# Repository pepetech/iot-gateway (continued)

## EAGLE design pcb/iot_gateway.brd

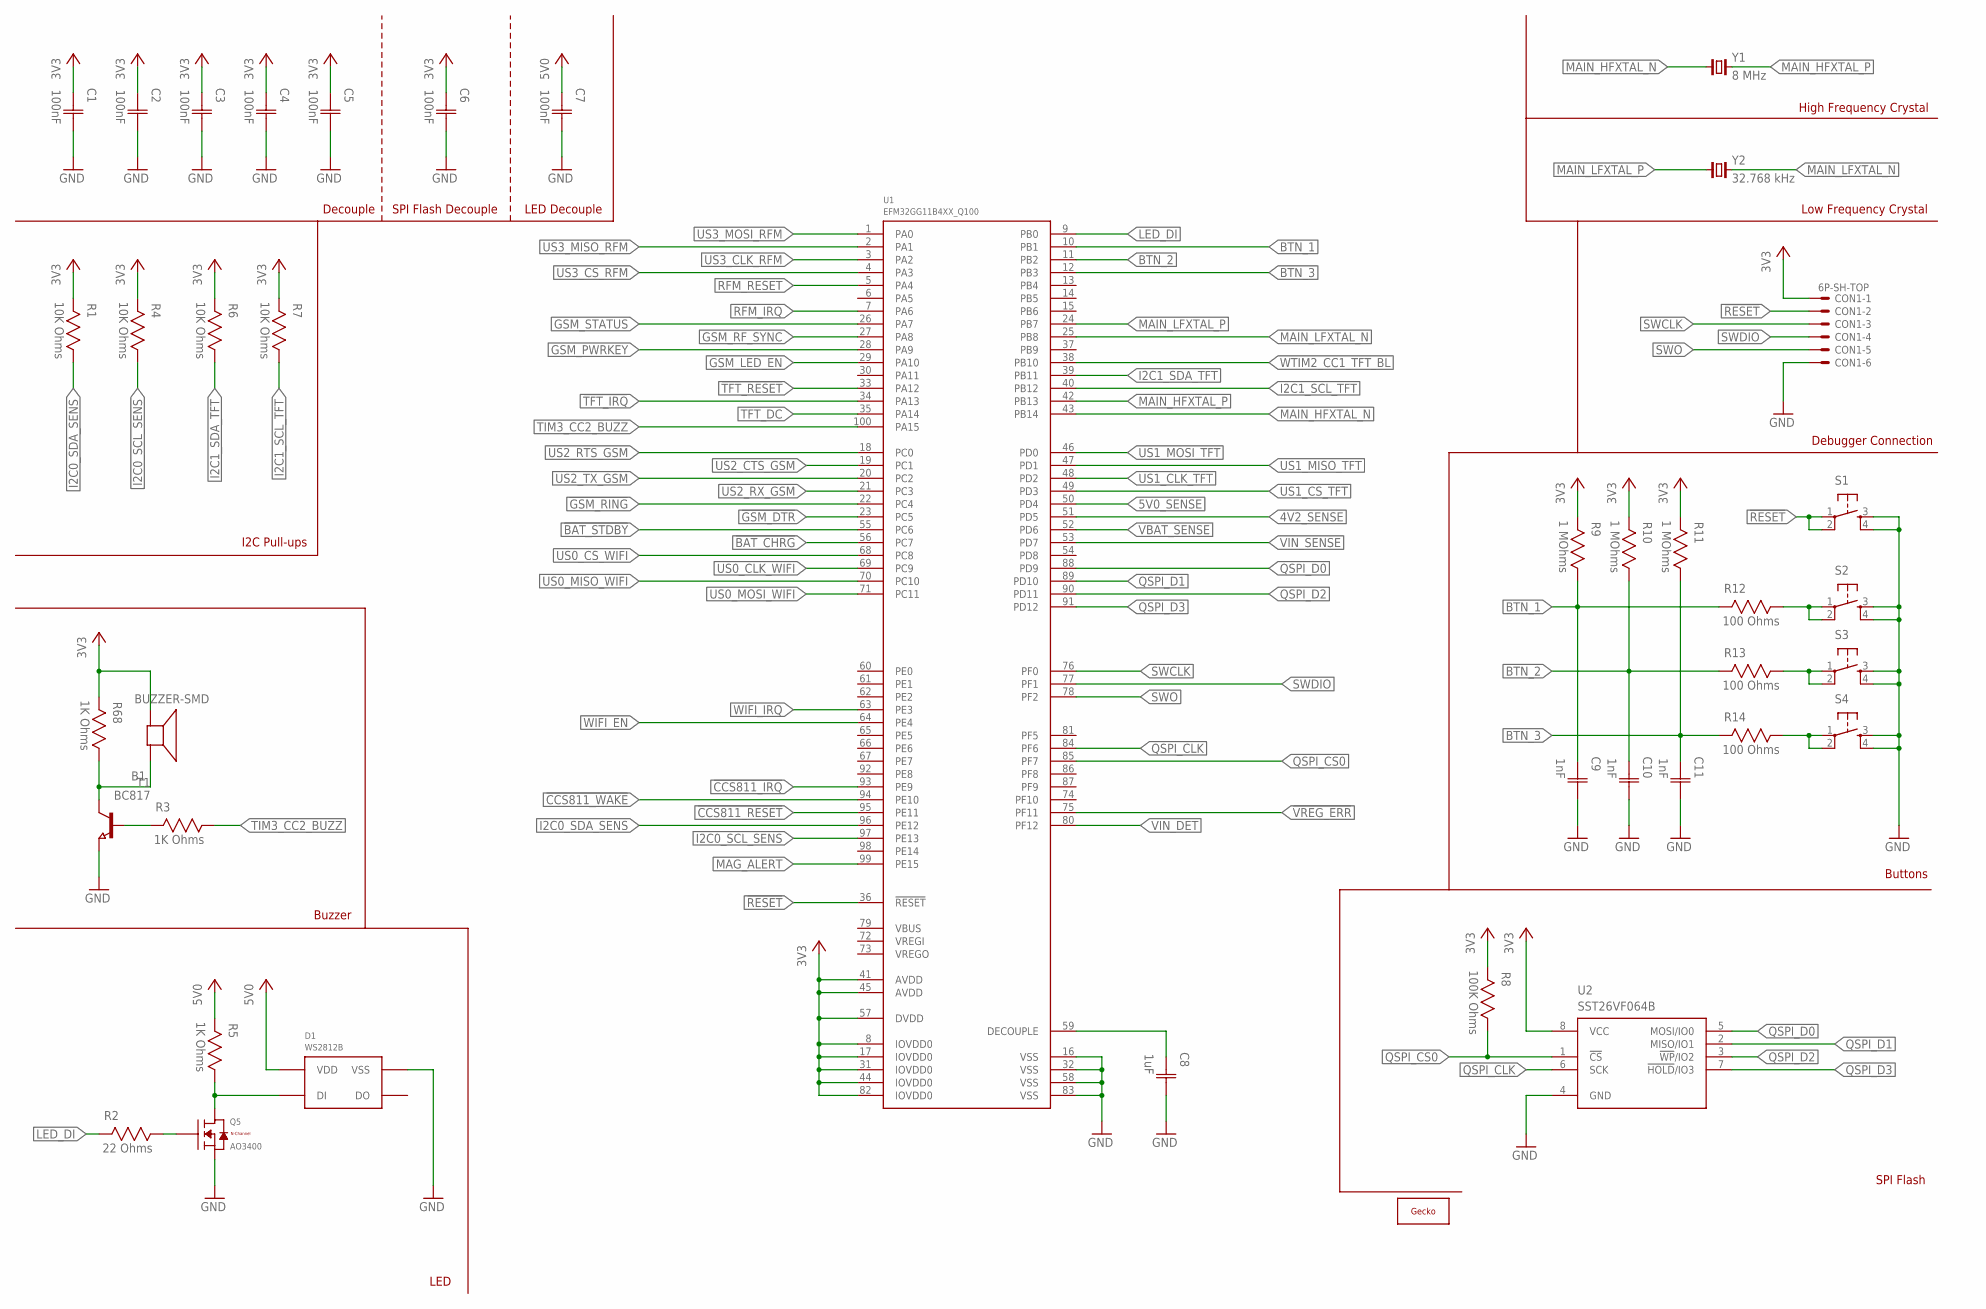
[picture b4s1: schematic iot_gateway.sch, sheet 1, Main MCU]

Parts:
B1: BUZZER-SMD; SMD
C1, C2, C3, C4, C5, C6, C7: 100nF; CAP0603
C8: 1uF; CAP0603
C9, C10, C11: 1nF; CAP0603
CON1: 6P-SH-TOP; SH-06-TOP
D1: WS2812B; WS2812B-SMD5050
Q5: AO3400; SOT23
R1, R4, R6, R7: 10K Ohms; RES0603
R2: 22 Ohms; RES0603
R3, R5, R68: 1K Ohms; RES0603
R8: 100K Ohms; RES0603
R9, R10, R11: 1 MOhms; RES0603
R12, R13, R14: 100 Ohms; RES0603
S1: TAC_SWITCHSMD; TAC_SW_SMD_RESET
S2, S3, S4: TAC_SWITCHSMD_4.5X4.5; TAC_SW_SMD_4.5X4.5
T1: BC817; SOT23
U1: EFM32GG11B4XX_Q100; QFP100
U2: SST26VF064B; WSOIC8
U$1: GECKO
Y1: 8 MHz; 2-SMD-5X3
Y2: 32.768 kHz; CM200S

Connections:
3V3: B1.1 (+), C1.1 (C1), C2.1 (C1), C3.1 (C1), C4.1 (C1), C5.1 (C1), C6.1 (C1), CON1.1, R1.2, R4.2, R6.2, R7.2, R8.2, R9.2, R10.2, R11.2, R68.2, U1.8 (IOVDD0), U1.17 (IOVDD0), U1.31 (IOVDD0), U1.41 (AVDD), U1.44 (IOVDD0), U1.45 (AVDD), U1.57 (DVDD), U1.82 (IOVDD0), U2.8 (VCC); also elsewhere on the board
4V2_SENSE: U1.51 (PD5); also elsewhere on the board
5V0: C7.1 (C1), D1.1 (VDD), R5.2; also elsewhere on the board
5V0_SENSE: U1.50 (PD4); also elsewhere on the board
!BAT_CHRG: U1.56 (PC7); also elsewhere on the board
!BAT_STDBY: U1.55 (PC6); also elsewhere on the board
!CCS811_IRQ: U1.93 (PE9); also elsewhere on the board
!CCS811_RESET: U1.95 (PE11); also elsewhere on the board
!CCS811_WAKE: U1.94 (PE10); also elsewhere on the board
!GSM_DTR: U1.23 (PC5); also elsewhere on the board
!GSM_RING: U1.22 (PC4); also elsewhere on the board
!RESET: CON1.2, S1.1, S1.2, U1.36 (!RESET)
!TFT_IRQ: U1.34 (PA13); also elsewhere on the board
!TFT_RESET: U1.33 (PA12); also elsewhere on the board
!VREG_ERR: U1.75 (PF11); also elsewhere on the board
BTN_1: C9.1 (C1), R9.1, R12.2, U1.10 (PB1)
BTN_2: C10.1 (C1), R10.1, R13.2, U1.11 (PB2)
BTN_3: C11.1 (C1), R11.1, R14.2, U1.12 (PB3)
GND: C1.2 (C2), C2.2 (C2), C3.2 (C2), C4.2 (C2), C5.2 (C2), C6.2 (C2), C7.2 (C2), C8.2 (C2), C9.2 (C2), C10.2 (C2), C11.2 (C2), CON1.6, D1.3 (VSS), Q5.2 (S), S1.3, S1.4, S2.3, S2.4, S3.3, S3.4, S4.3, S4.4, T1.2 (E), U1.16 (VSS), U1.32 (VSS), U1.58 (VSS), U1.83 (VSS), U2.4 (GND); also elsewhere on the board
GSM_LED_EN: U1.29 (PA10); also elsewhere on the board
GSM_PWRKEY: U1.28 (PA9); also elsewhere on the board
GSM_RF_SYNC: U1.27 (PA8); also elsewhere on the board
GSM_STATUS: U1.26 (PA7); also elsewhere on the board
I2C0_SCL_SENS: R4.1, U1.97 (PE13); also elsewhere on the board
I2C0_SDA_SENS: R1.1, U1.96 (PE12); also elsewhere on the board
I2C1_SCL_TFT: R7.1, U1.40 (PB12); also elsewhere on the board
I2C1_SDA_TFT: R6.1, U1.39 (PB11); also elsewhere on the board
LED_DI: R2.2, U1.9 (PB0)
MAG_ALERT: U1.99 (PE15); also elsewhere on the board
MAIN_HFXTAL_N: U1.43 (PB14), Y1.1
MAIN_HFXTAL_P: U1.42 (PB13), Y1.2
MAIN_LFXTAL_N: U1.25 (PB8), Y2.4 (2)
MAIN_LFXTAL_P: U1.24 (PB7), Y2.1
unnamed: C8.1 (C1), U1.59 (DECOUPLE)
unnamed: D1.4 (DI), Q5.3 (D), R5.1
unnamed: Q5.1 (G), R2.1
unnamed: R3.2, T1.1 (B)
unnamed: B1.2 (-), R68.1, T1.3 (C)
unnamed: R12.1, S2.1, S2.2
unnamed: R13.1, S3.1, S3.2
unnamed: R14.1, S4.1, S4.2
QSPI_CLK: U1.84 (PF6), U2.6 (SCK)
QSPI_CS0: R8.1, U1.85 (PF7), U2.1 (!CS!)
QSPI_D0: U1.88 (PD9), U2.5 (MOSI/IO0)
QSPI_D1: U1.89 (PD10), U2.2 (MISO/IO1)
QSPI_D2: U1.90 (PD11), U2.3 (!WP!/IO2)
QSPI_D3: U1.91 (PD12), U2.7 (!HOLD!/IO3)
RFM_IRQ: U1.7 (PA6); also elsewhere on the board
RFM_RESET: U1.5 (PA4); also elsewhere on the board
SWCLK: CON1.3, U1.76 (PF0)
SWDIO: CON1.4, U1.77 (PF1)
SWO: CON1.5, U1.78 (PF2)
TFT_DC: U1.35 (PA14); also elsewhere on the board
TIM3_CC2_BUZZ: R3.1, U1.100 (PA15)
US0_CLK_WIFI: U1.69 (PC9); also elsewhere on the board
US0_CS_WIFI: U1.68 (PC8); also elsewhere on the board
US0_MISO_WIFI: U1.70 (PC10); also elsewhere on the board
US0_MOSI_WIFI: U1.71 (PC11); also elsewhere on the board
US1_CLK_TFT: U1.48 (PD2); also elsewhere on the board
US1_CS_TFT: U1.49 (PD3); also elsewhere on the board
US1_MISO_TFT: U1.47 (PD1); also elsewhere on the board
US1_MOSI_TFT: U1.46 (PD0); also elsewhere on the board
US2_CTS_GSM: U1.19 (PC1); also elsewhere on the board
US2_RTS_GSM: U1.18 (PC0); also elsewhere on the board
US2_RX_GSM: U1.21 (PC3); also elsewhere on the board
US2_TX_GSM: U1.20 (PC2); also elsewhere on the board
US3_CLK_RFM: U1.3 (PA2); also elsewhere on the board
US3_CS_RFM: U1.4 (PA3); also elsewhere on the board
US3_MISO_RFM: U1.2 (PA1); also elsewhere on the board
US3_MOSI_RFM: U1.1 (PA0); also elsewhere on the board
VBAT_SENSE: U1.52 (PD6); also elsewhere on the board
VIN_DET: U1.80 (PF12); also elsewhere on the board
VIN_SENSE: U1.53 (PD7); also elsewhere on the board
WIFI_EN: U1.64 (PE4); also elsewhere on the board
WIFI_IRQ: U1.63 (PE3); also elsewhere on the board
WTIM2_CC1_TFT_BL: U1.38 (PB10); also elsewhere on the board

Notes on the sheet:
High Frequency Crystal
Low Frequency Crystal
Decouple
I2C Pull-ups
Debugger Connection
Buzzer
LED
SPI Flash
SPI Flash Decouple
LED Decouple
Buttons

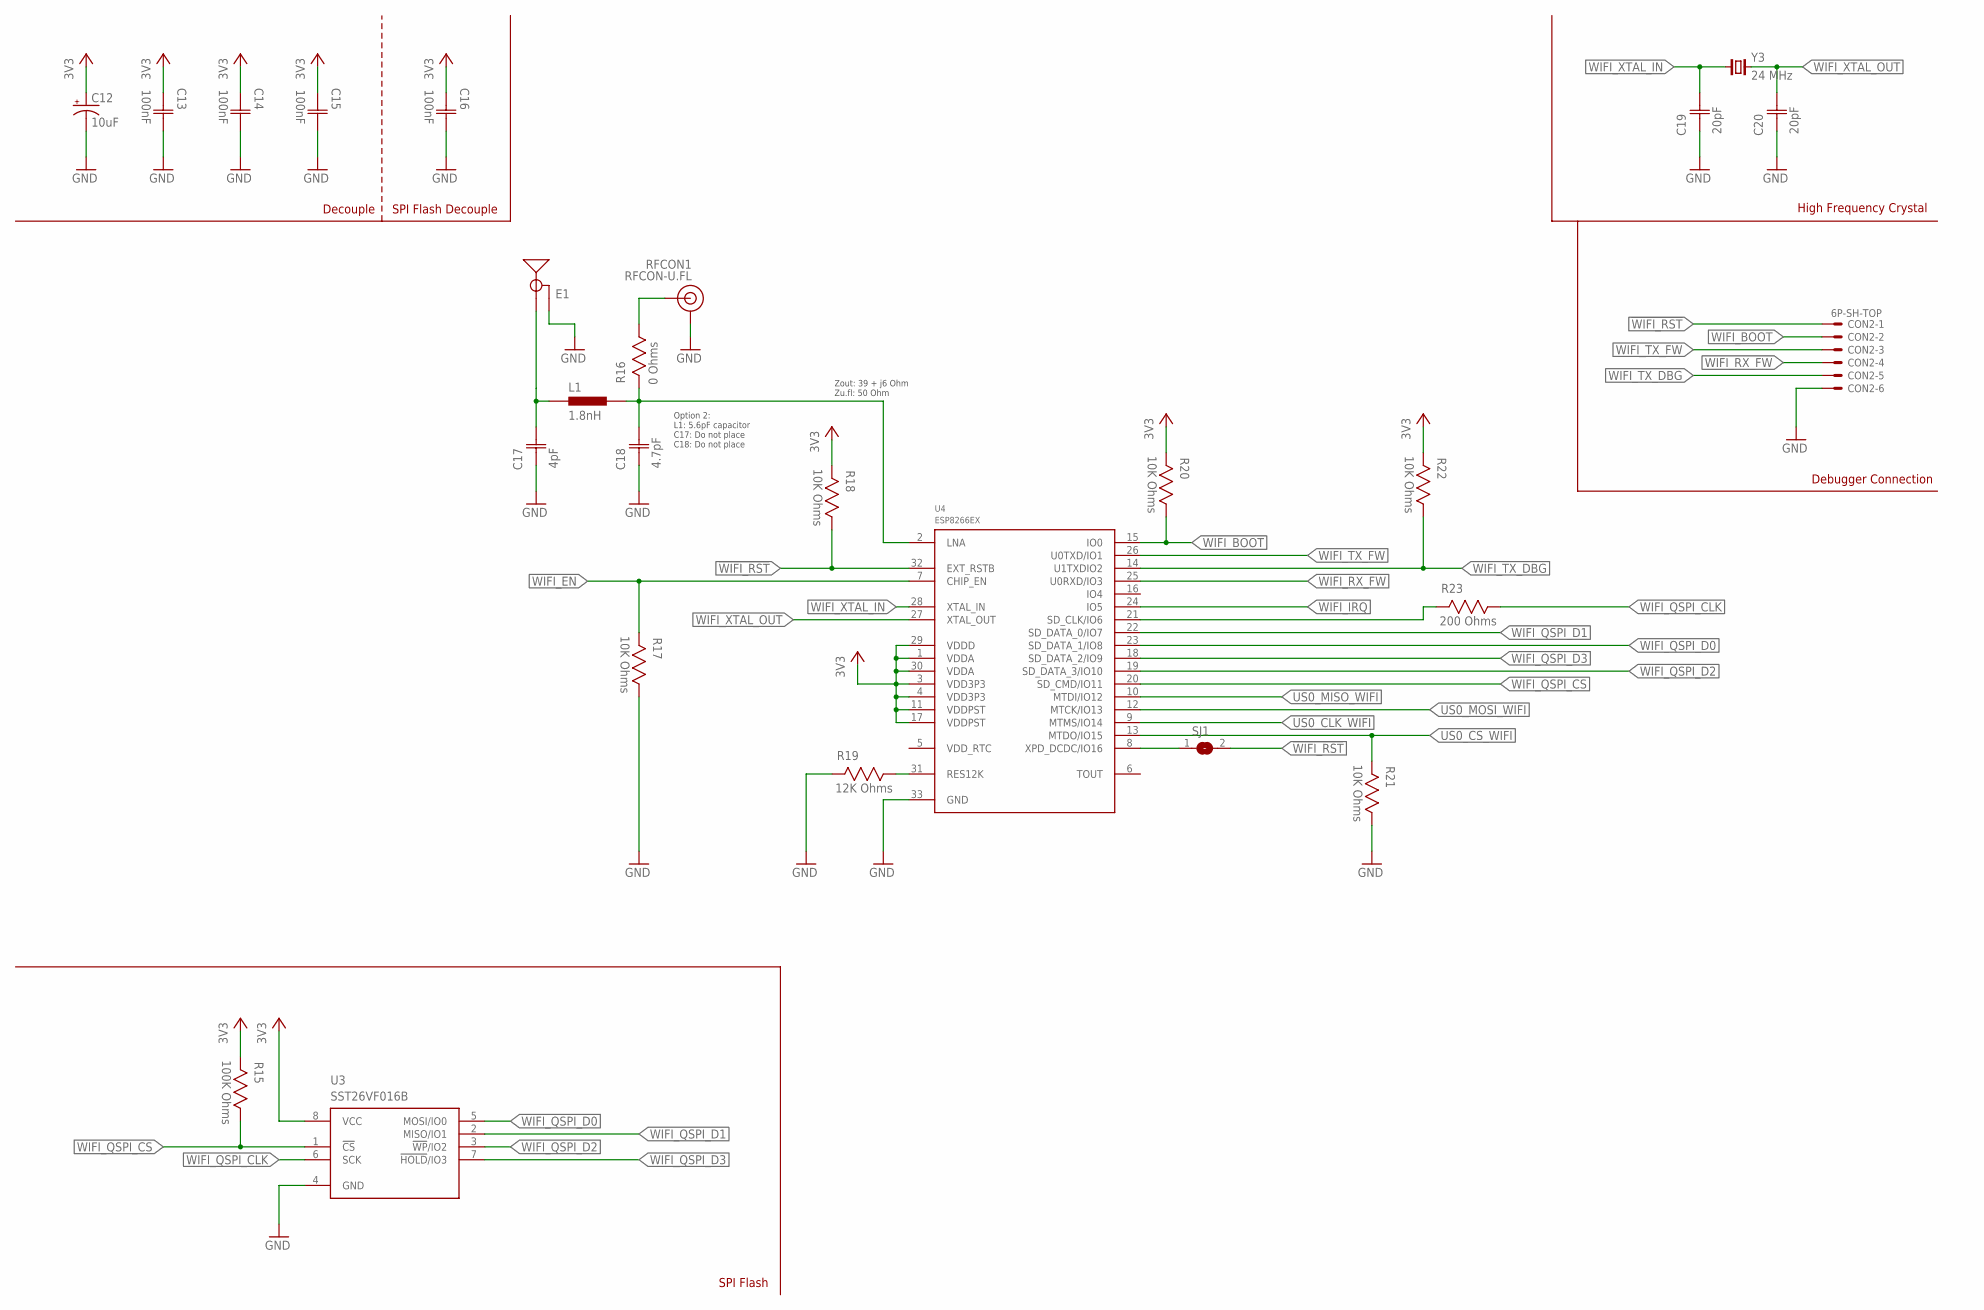
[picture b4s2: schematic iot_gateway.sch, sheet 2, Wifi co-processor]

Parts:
C12: 10uF; TAN-CAP-CASE-A
C13, C14, C15, C16: 100nF; CAP0603
C17: 4pF; CAP0603
C18: 4.7pF; CAP0603
C19, C20: 20pF; CAP0603
CON2: 6P-SH-TOP; SH-06-TOP
E1: 2.4GHZTRACE-15.2MM; TRACE_ANTENNA_2.4GHZ_15.2MM
L1: 1.8nH; IND0603
R15: 100K Ohms; RES0603
R16: 0 Ohms; RES0603
R17, R18, R20, R21, R22: 10K Ohms; RES0603
R19: 12K Ohms; RES0603
R23: 200 Ohms; RES0603
RFCON1: RFCON-U.FL; U.FL
SJ1: SJS; SJ_S
U3: SST26VF016B; WSOIC8
U4: ESP8266EX; QFN32
Y3: 24 MHz; 2-SMD-5X3

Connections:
3V3: C12.A (+), C13.1 (C1), C14.1 (C1), C15.1 (C1), C16.1 (C1), R15.2, R18.2, R20.2, R22.2, U3.8 (VCC), U4.1 (VDDA), U4.3 (VDD3P3), U4.4 (VDD3P3), U4.11 (VDDPST), U4.17 (VDDPST), U4.29 (VDDD), U4.30 (VDDA); also elsewhere on the board
!WIFI_RST: CON2.1, R18.1, SJ1.2, U4.32 (EXT_RSTB)
GND: C12.C (-), C13.2 (C2), C14.2 (C2), C15.2 (C2), C16.2 (C2), C17.1 (C1), C18.1 (C1), C19.1 (C1), C20.1 (C1), CON2.6, E1.GND, R17.1, R19.2, R21.1, RFCON1.P$1 (GND), RFCON1.P$2 (GND), U3.4 (GND), U4.33 (GND); also elsewhere on the board
unnamed: R19.1, U4.31 (RES12K)
unnamed: R23.2, U4.21 (SD_CLK/IO6)
unnamed: C18.2 (C2), L1.2, R16.2, U4.2 (LNA)
unnamed: C17.2 (C2), E1.ANT (SIGNAL), L1.1
unnamed: R16.1, RFCON1.P$3 (SIGNAL)
unnamed: SJ1.1, U4.8 (XPD_DCDC/IO16)
US0_CLK_WIFI: U4.9 (MTMS/IO14); also elsewhere on the board
US0_CS_WIFI: R21.2, U4.13 (MTDO/IO15); also elsewhere on the board
US0_MISO_WIFI: U4.10 (MTDI/IO12); also elsewhere on the board
US0_MOSI_WIFI: U4.12 (MTCK/IO13); also elsewhere on the board
WIFI_BOOT: CON2.2, R20.1, U4.15 (IO0)
WIFI_EN: R17.2, U4.7 (CHIP_EN); also elsewhere on the board
WIFI_IRQ: U4.24 (IO5); also elsewhere on the board
WIFI_QSPI_CLK: R23.1, U3.6 (SCK)
WIFI_QSPI_CS: R15.1, U3.1 (!CS!), U4.20 (SD_CMD/IO11)
WIFI_QSPI_D0: U3.5 (MOSI/IO0), U4.23 (SD_DATA_1/IO8)
WIFI_QSPI_D1: U3.2 (MISO/IO1), U4.22 (SD_DATA_0/IO7)
WIFI_QSPI_D2: U3.3 (!WP!/IO2), U4.19 (SD_DATA_3/IO10)
WIFI_QSPI_D3: U3.7 (!HOLD!/IO3), U4.18 (SD_DATA_2/IO9)
WIFI_RX_FW: CON2.4, U4.25 (U0RXD/IO3)
WIFI_TX_DBG: CON2.5, R22.1, U4.14 (U1TXDIO2)
WIFI_TX_FW: CON2.3, U4.26 (U0TXD/IO1)
WIFI_XTAL_IN: C19.2 (C2), U4.28 (XTAL_IN), Y3.1
WIFI_XTAL_OUT: C20.2 (C2), U4.27 (XTAL_OUT), Y3.2

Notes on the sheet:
SPI Flash
Option 2: L1: 5.6pF capacitor C17: Do not place C18: Do not place
Zout: 39 + j6 Ohm Zu.fl: 50 Ohm
High Frequency Crystal
Decouple
SPI Flash Decouple
Debugger Connection

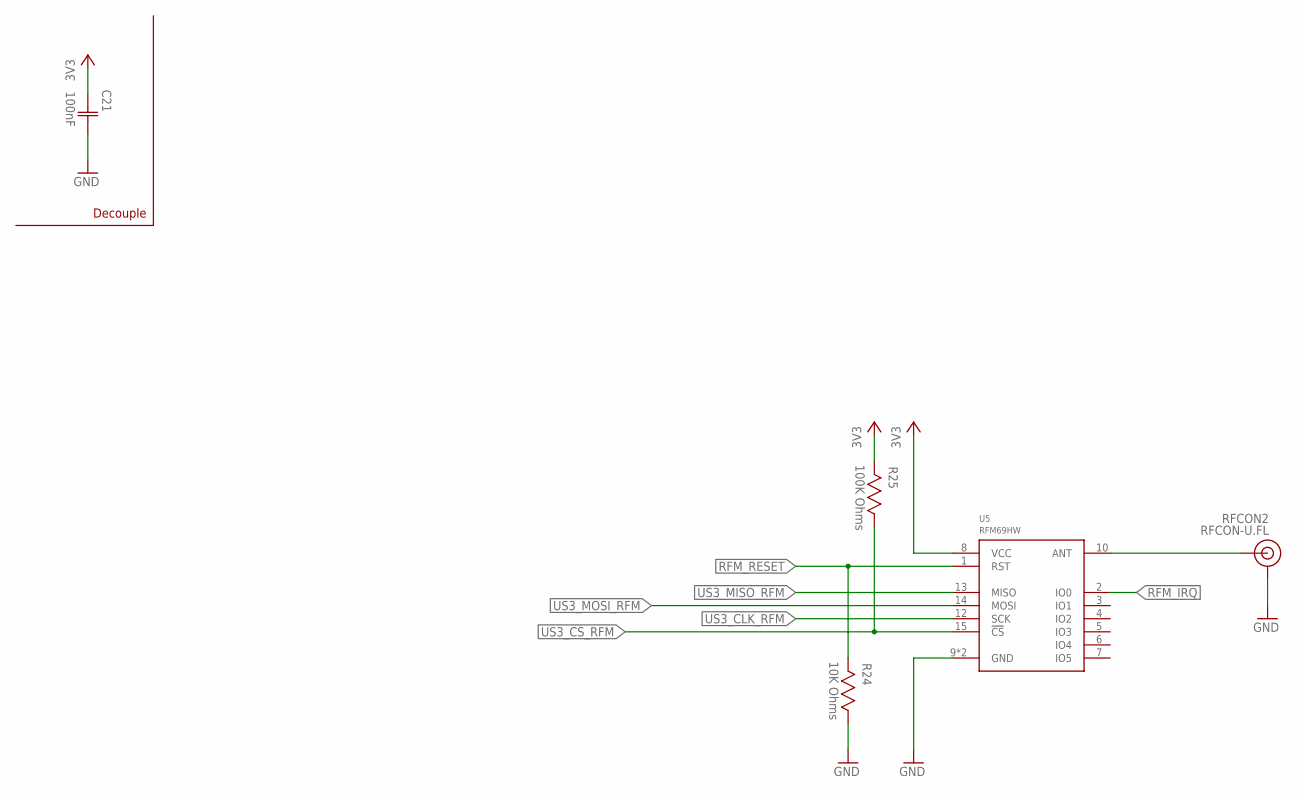
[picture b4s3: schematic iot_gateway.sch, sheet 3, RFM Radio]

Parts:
C21: 100nF; CAP0603
R24: 10K Ohms; RES0603
R25: 100K Ohms; RES0603
RFCON2: RFCON-U.FL; U.FL
U5: RFM69HW; RFM69W-XXXS2

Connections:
3V3: C21.1 (C1), R25.2, U5.8 (VCC); also elsewhere on the board
GND: C21.2 (C2), R24.1, RFCON2.P$1 (GND), RFCON2.P$2 (GND), U5.9 (GND), U5.11 (GND); also elsewhere on the board
unnamed: RFCON2.P$3 (SIGNAL), U5.10 (ANT)
RFM_IRQ: U5.2 (IO0); also elsewhere on the board
RFM_RESET: R24.2, U5.1 (RST); also elsewhere on the board
US3_CLK_RFM: U5.12 (SCK); also elsewhere on the board
US3_CS_RFM: R25.1, U5.15 (!CS); also elsewhere on the board
US3_MISO_RFM: U5.13 (MISO); also elsewhere on the board
US3_MOSI_RFM: U5.14 (MOSI); also elsewhere on the board

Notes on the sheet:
Decouple

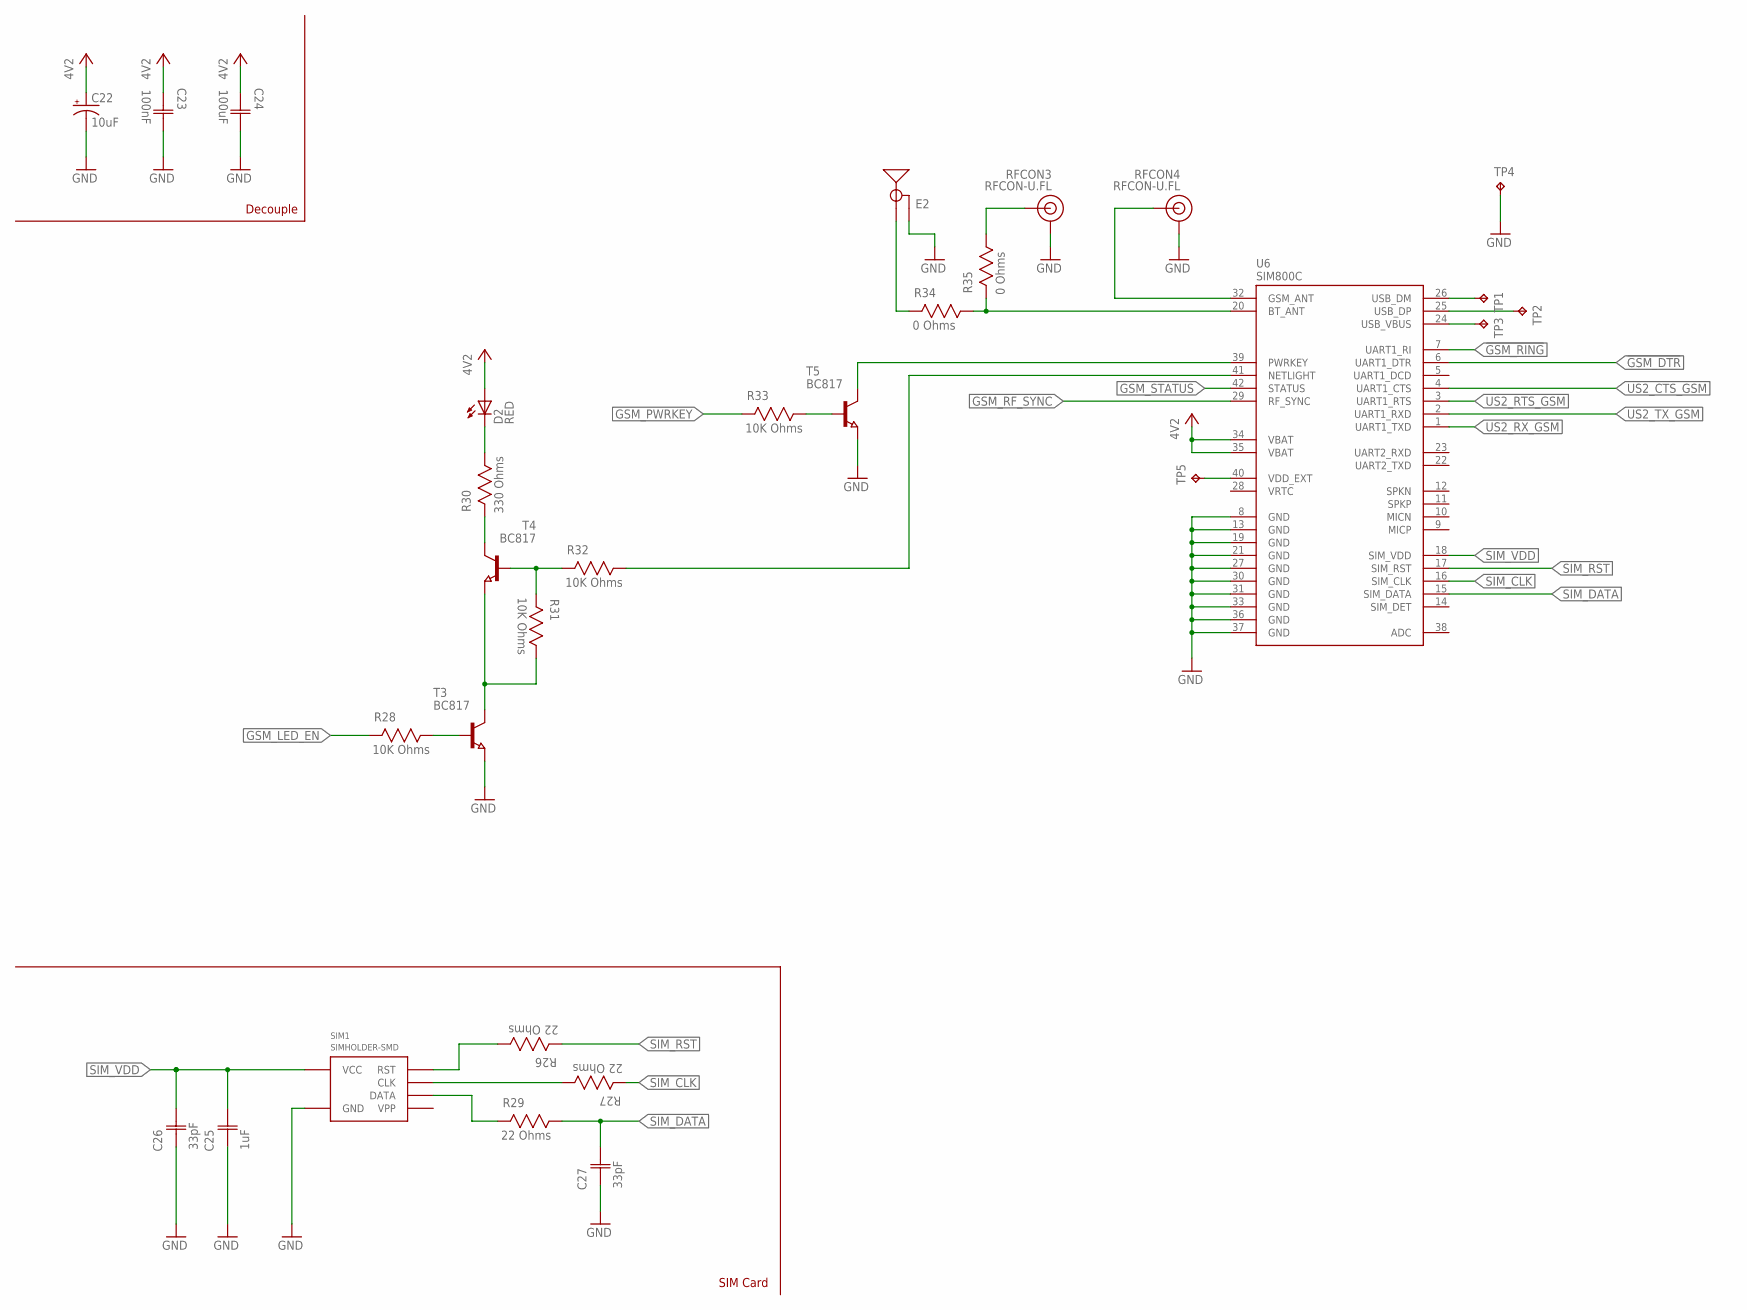
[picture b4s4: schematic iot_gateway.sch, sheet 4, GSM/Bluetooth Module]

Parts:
C22: 10uF; TAN-CAP-CASE-A
C23: 100nF; CAP0603
C24: 100uF; CAP1206
C25: 1uF; CAP0603
C26, C27: 33pF; CAP0603
D2: RED; 1206
E2: 2.4GHZTRACE-15.2MM; TRACE_ANTENNA_2.4GHZ_15.2MM
R26, R27, R29: 22 Ohms; RES0603
R28, R31, R32, R33: 10K Ohms; RES0603
R30: 330 Ohms; RES0603
R34, R35: 0 Ohms; RES0603
RFCON3, RFCON4: RFCON-U.FL; U.FL
SIM1: SIMHOLDER-SMD
T3, T4, T5: BC817; SOT23
TP1, TP2, TP3, TP4, TP5: TESTPOINT; PAD1.27MM
U6: SIM800C

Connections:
4V2: C22.A (+), C23.1 (C1), C24.1 (C1), D2.2 (A), U6.34 (VBAT), U6.35 (VBAT); also elsewhere on the board
!GSM_DTR: U6.6 (UART1_DTR); also elsewhere on the board
!GSM_RING: U6.7 (UART1_RI); also elsewhere on the board
GND: C22.C (-), C23.2 (C2), C24.2 (C2), C25.1 (C1), C26.1 (C1), C27.1 (C1), E2.GND, RFCON3.P$1 (GND), RFCON3.P$2 (GND), RFCON4.P$1 (GND), RFCON4.P$2 (GND), SIM1.C5 (GND), T3.2 (E), T5.2 (E), TP4.TP, U6.8 (GND), U6.13 (GND), U6.19 (GND), U6.21 (GND), U6.27 (GND), U6.30 (GND), U6.31 (GND), U6.33 (GND), U6.36 (GND), U6.37 (GND); also elsewhere on the board
GSM_LED_EN: R28.2; also elsewhere on the board
GSM_PWRKEY: R33.2; also elsewhere on the board
GSM_RF_SYNC: U6.29 (RF_SYNC); also elsewhere on the board
GSM_STATUS: U6.42 (STATUS); also elsewhere on the board
unnamed: RFCON4.P$3 (SIGNAL), U6.32 (GSM_ANT)
unnamed: R26.1, SIM1.C2 (RST)
unnamed: R32.1, U6.41 (NETLIGHT)
unnamed: R31.2, R32.2, T4.1 (B)
unnamed: R30.2, T4.3 (C)
unnamed: R27.1, SIM1.C3 (CLK)
unnamed: R34.1, R35.2, U6.20 (BT_ANT)
unnamed: E2.ANT (SIGNAL), R34.2
unnamed: R35.1, RFCON3.P$3 (SIGNAL)
unnamed: R31.1, T3.3 (C), T4.2 (E)
unnamed: D2.1 (C), R30.1
unnamed: TP1.TP, U6.26 (USB_DM)
unnamed: TP2.TP, U6.25 (USB_DP)
unnamed: T5.3 (C), U6.39 (PWRKEY)
unnamed: R33.1, T5.1 (B)
unnamed: R28.1, T3.1 (B)
unnamed: TP3.TP, U6.24 (USB_VBUS)
unnamed: TP5.TP, U6.40 (VDD_EXT)
unnamed: R29.2, SIM1.C7 (DATA)
SIM_CLK: R27.2, U6.16 (SIM_CLK)
SIM_DATA: C27.2 (C2), R29.1, U6.15 (SIM_DATA)
SIM_RST: R26.2, U6.17 (SIM_RST)
SIM_VDD: C25.2 (C2), C26.2 (C2), SIM1.C1 (VCC), U6.18 (SIM_VDD)
US2_CTS_GSM: U6.4 (UART1_CTS); also elsewhere on the board
US2_RTS_GSM: U6.3 (UART1_RTS); also elsewhere on the board
US2_RX_GSM: U6.1 (UART1_TXD); also elsewhere on the board
US2_TX_GSM: U6.2 (UART1_RXD); also elsewhere on the board

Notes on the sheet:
Decouple
SIM Card

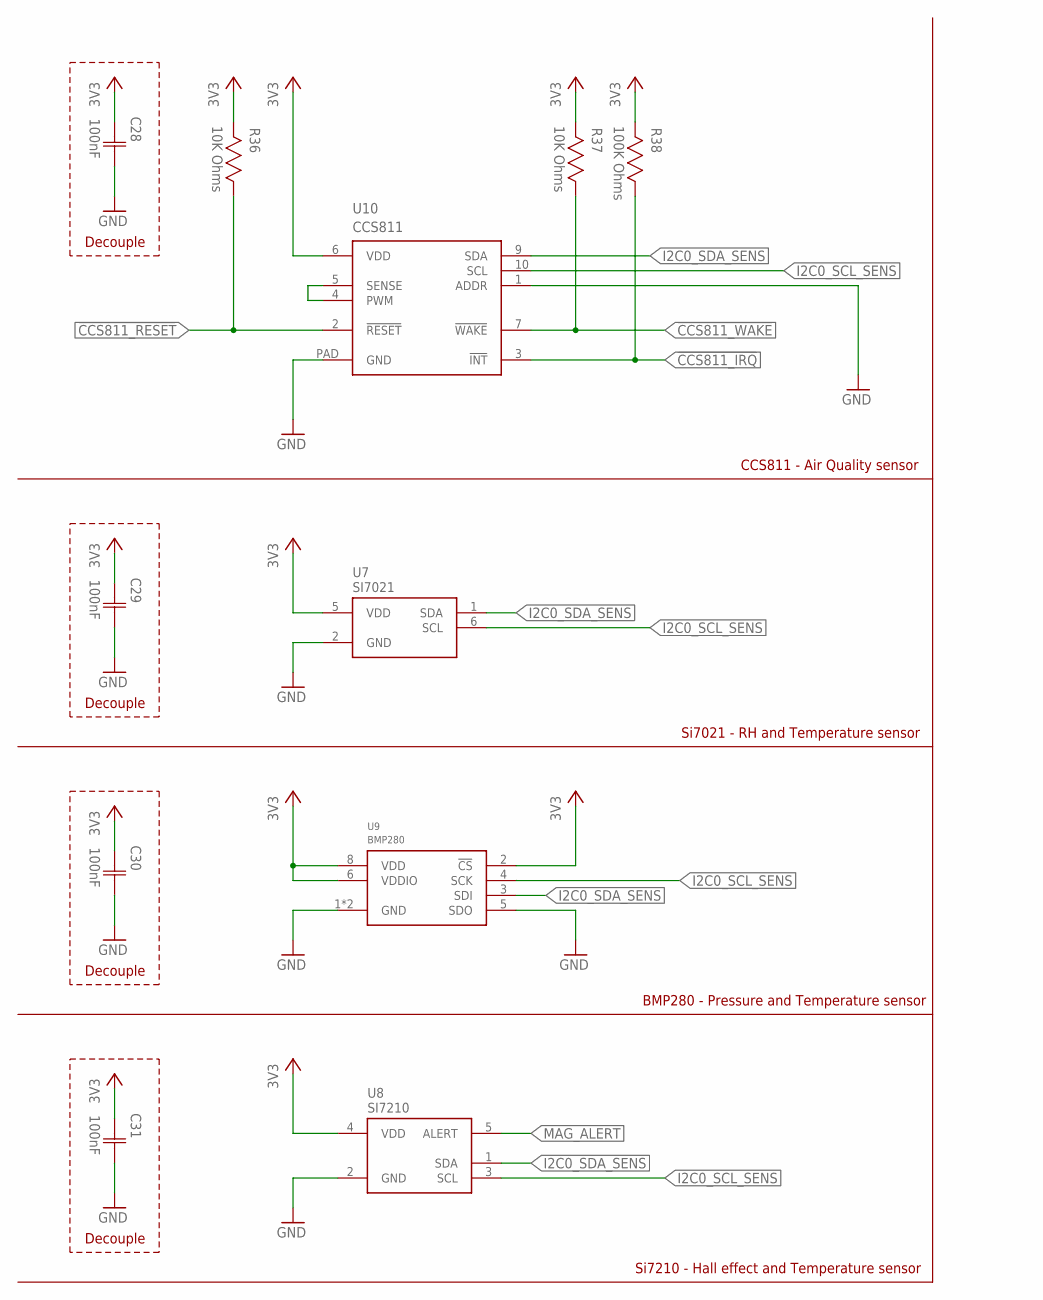
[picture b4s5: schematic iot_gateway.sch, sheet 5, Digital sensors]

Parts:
C28, C29, C30, C31: 100nF; CAP0603
R36, R37: 10K Ohms; RES0603
R38: 100K Ohms; RES0603
U7: SI7021; DFN6
U8: SI7210; SOT23-5
U9: BMP280
U10: CCS811; LGA10

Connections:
3V3: C28.1 (C1), C29.1 (C1), C30.1 (C1), C31.1 (C1), R36.2, R37.2, R38.2, U7.5 (VDD), U8.4 (VDD), U9.2 (!CS), U9.6 (VDDIO), U9.8 (VDD), U10.6 (VDD); also elsewhere on the board
!CCS811_IRQ: R38.1, U10.3 (!INT); also elsewhere on the board
!CCS811_RESET: R36.1, U10.2 (!RESET); also elsewhere on the board
!CCS811_WAKE: R37.1, U10.7 (!WAKE); also elsewhere on the board
GND: C28.2 (C2), C29.2 (C2), C30.2 (C2), C31.2 (C2), U7.2 (GND), U8.2 (GND), U9.1 (GND), U9.5 (SDO), U9.7 (GND), U10.1 (ADDR), U10.PAD (GND); also elsewhere on the board
I2C0_SCL_SENS: U7.6 (SCL), U8.3 (SCL), U9.4 (SCK), U10.10 (SCL); also elsewhere on the board
I2C0_SDA_SENS: U7.1 (SDA), U8.1 (SDA), U9.3 (SDI), U10.9 (SDA); also elsewhere on the board
MAG_ALERT: U8.5 (ALERT); also elsewhere on the board
unnamed: U10.4 (PWM), U10.5 (SENSE)

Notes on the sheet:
CCS811 - Air Quality sensor
Decouple
Si7021 - RH and Temperature sensor
BMP280 - Pressure and Temperature sensor
Si7210 - Hall effect and Temperature sensor

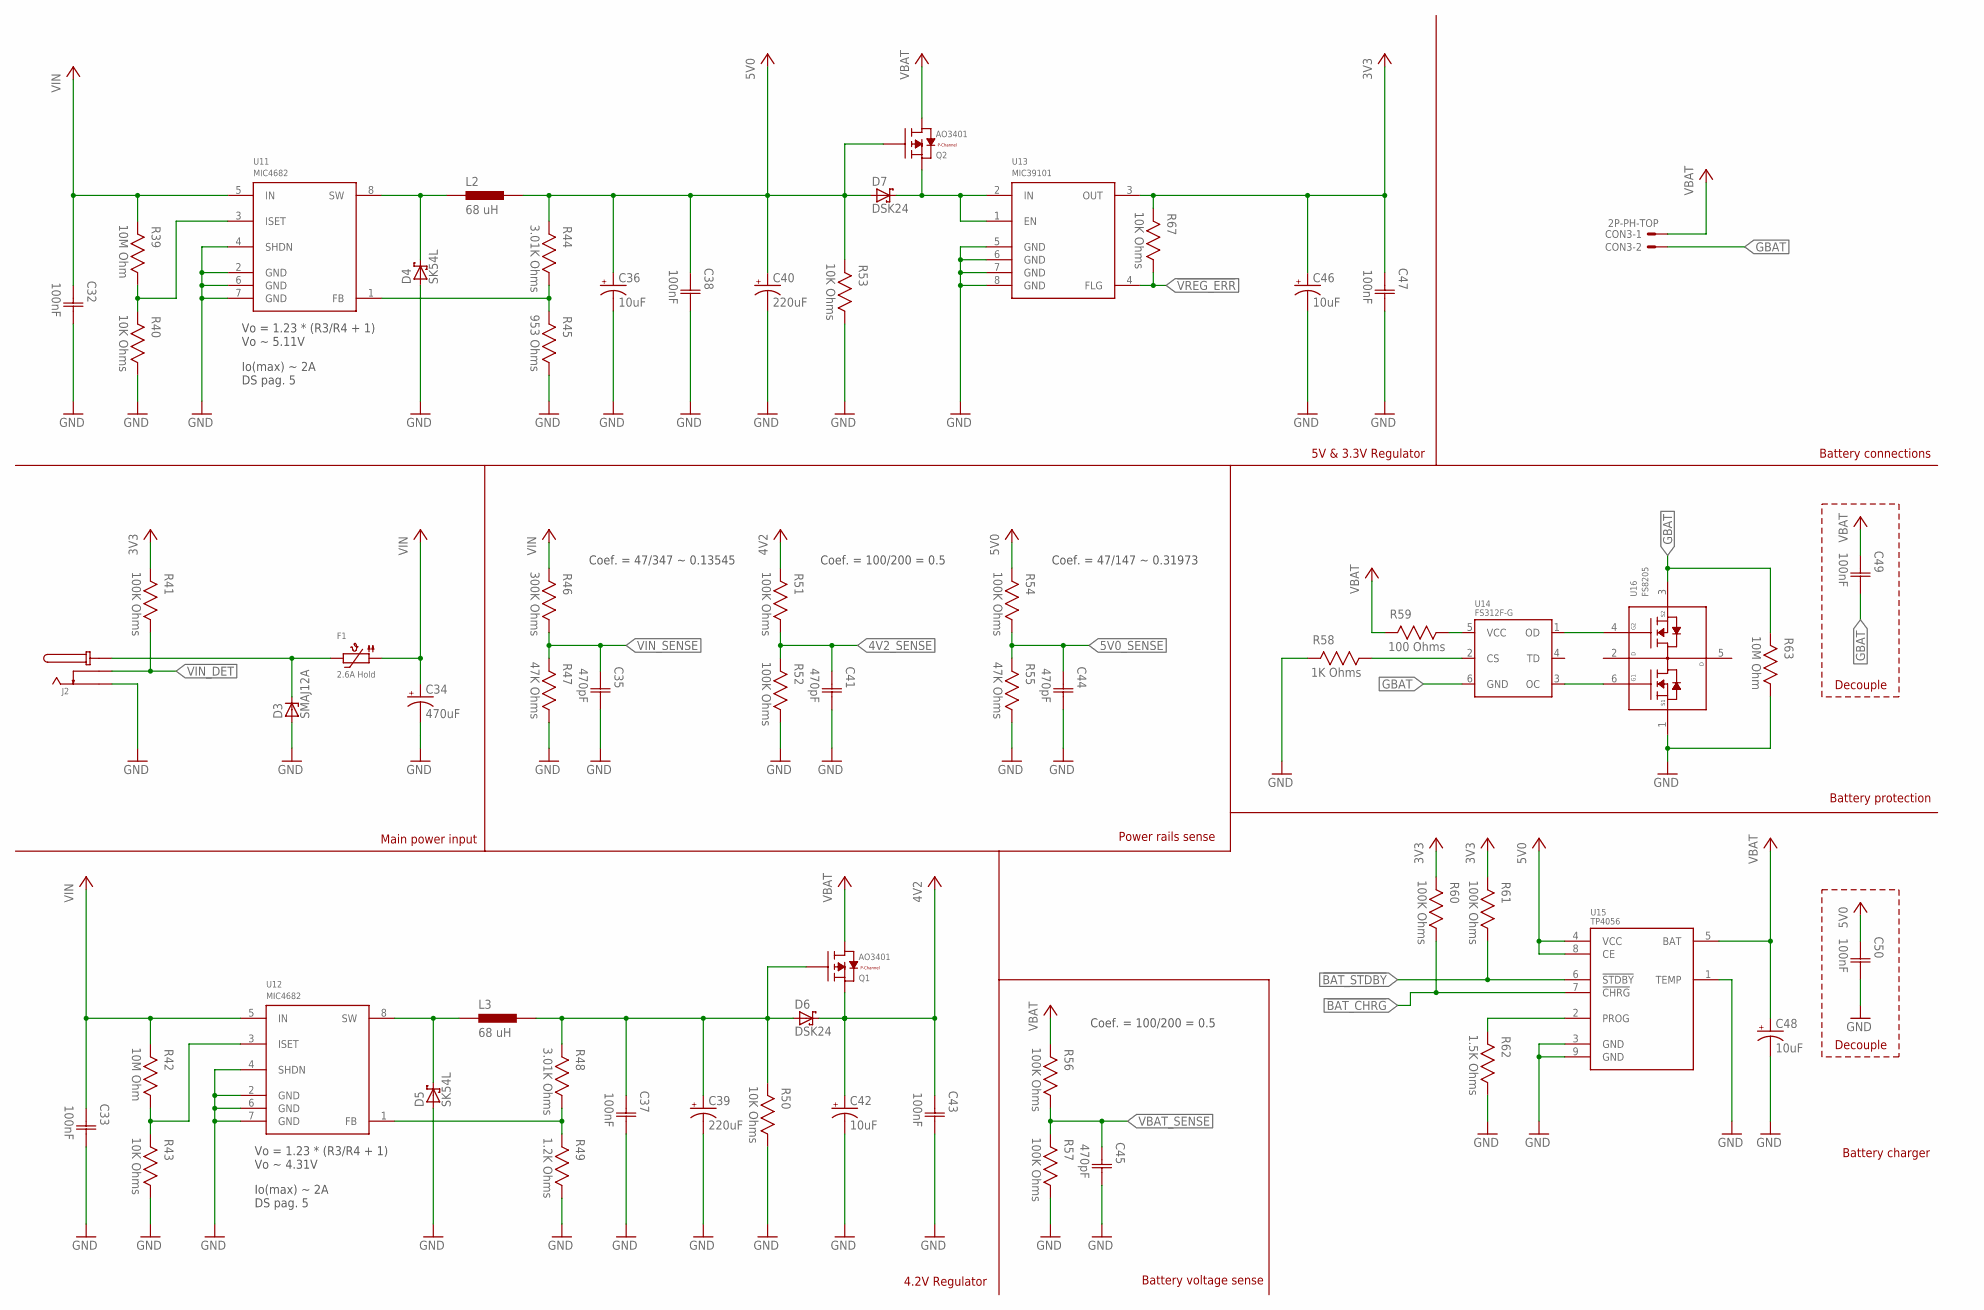
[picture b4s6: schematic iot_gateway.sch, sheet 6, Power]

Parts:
C32, C33, C37, C38, C43, C47, C49, C50: 100nF; CAP0603
C34: 470uF; AL-CAP-CASE-F
C35, C41, C44, C45: 470pF; CAP0603
C36, C42, C46, C48: 10uF; TAN-CAP-CASE-A
C39, C40: 220uF; AL-CAP-CASE-D
CON3: 2P-PH-TOP; PH-02-TOP
D3: SMAJ12A; DO214AC
D4, D5: SK54L; DO214AA
D6, D7: DSK24; SOD-123
F1: 2.6A Hold; 1812
J2: DCJACK-SMD; SMD
L2, L3: 68 uH; IND1207
Q1, Q2: AO3401; SOT23
R39, R42, R63: 10M Ohm; RES0603
R40, R43, R50, R53, R67: 10K Ohms; RES0603
R41, R51, R52, R54, R56, R57, R60, R61: 100K Ohms; RES0603
R44, R48: 3.01K Ohms; RES0603
R45: 953 Ohms; RES0603
R46: 300K Ohms; RES0603
R47, R55: 47K Ohms; RES0603
R49: 1.2K Ohms; RES0603
R58: 1K Ohms; RES0603
R59: 100 Ohms; RES0603
R62: 1.5K Ohms; RES0603
U11, U12: MIC4682; SOIC8
U13: MIC39101; SOIC8
U14: FS312F-G; SOT23-6
U15: TP4056; SOP-8
U16: FS8205; SOT23-6

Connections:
3V3: C46.A (+), C47.1 (C1), R41.2, R60.2, R61.2, R67.2, U13.3 (OUT); also elsewhere on the board
4V2: C42.A (+), C43.1 (C1), D6.C, Q1.2 (S), R51.2; also elsewhere on the board
4V2_SENSE: C41.1 (C1), R51.1, R52.2; also elsewhere on the board
5V0: C36.A (+), C38.1 (C1), C40.1 (+), C50.1 (C1), D7.A, L2.2, Q2.1 (G), R44.2, R53.2, R54.2, U15.4 (VCC), U15.8 (CE); also elsewhere on the board
5V0_SENSE: C44.1 (C1), R54.1, R55.2; also elsewhere on the board
!BAT_CHRG: R60.1, U15.7 (!CHRG); also elsewhere on the board
!BAT_STDBY: R61.1, U15.6 (!STDBY); also elsewhere on the board
!VREG_ERR: R67.1, U13.4 (FLG); also elsewhere on the board
GBAT: C49.2 (C2), CON3.2, R63.2, U14.6 (GND), U16.3 (S2)
GND: C32.2 (C2), C33.2 (C2), C34.2 (-), C35.2 (C2), C36.C (-), C37.2 (C2), C38.2 (C2), C39.2 (-), C40.2 (-), C41.2 (C2), C42.C (-), C43.2 (C2), C44.2 (C2), C45.2 (C2), C46.C (-), C47.2 (C2), C48.C (-), C50.2 (C2), D3.A, D4.A, D5.A, J2.2, R40.1, R43.1, R45.1, R47.1, R49.1, R50.1, R52.1, R53.1, R55.1, R57.1, R58.2, R62.1, R63.1, U11.2 (GND), U11.4 (SHDN), U11.6 (GND), U11.7 (GND), U12.2 (GND), U12.4 (SHDN), U12.6 (GND), U12.7 (GND), U13.5 (GND), U13.6 (GND), U13.7 (GND), U13.8 (GND), U15.1 (TEMP), U15.3 (GND), U15.9 (GND), U16.1 (S1); also elsewhere on the board
unnamed: D4.C, L2.1, U11.8 (SW)
unnamed: R44.1, R45.2, U11.1 (FB)
unnamed: R39.1, R40.2, U11.3 (ISET)
unnamed: D5.C, L3.1, U12.8 (SW)
unnamed: R48.1, R49.2, U12.1 (FB)
unnamed: R42.1, R43.2, U12.3 (ISET)
unnamed: C37.1 (C1), C39.1 (+), D6.A, L3.2, Q1.1 (G), R48.2, R50.2
unnamed: D7.C, Q2.2 (S), U13.1 (EN), U13.2 (IN)
unnamed: R62.2, U15.2 (PROG)
unnamed: U14.3 (OC), U16.6 (G1)
unnamed: U14.1 (OD), U16.4 (G2)
unnamed: R59.1, U14.5 (VCC)
unnamed: R58.1, U14.2 (CS)
unnamed: D3.C, F1.2, J2.1, J2.1' (1)
VBAT: C48.A (+), C49.1 (C1), CON3.1, Q1.3 (D), Q2.3 (D), R56.2, R59.2, U15.5 (BAT)
VBAT_SENSE: C45.1 (C1), R56.1, R57.2; also elsewhere on the board
VIN: C32.1 (C1), C33.1 (C1), C34.1 (+), F1.1, R39.2, R42.2, R46.2, U11.5 (IN), U12.5 (IN)
VIN_DET: J2.3, R41.1; also elsewhere on the board
VIN_SENSE: C35.1 (C1), R46.1, R47.2; also elsewhere on the board

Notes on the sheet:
Vo = 1.23 * (R3/R4 + 1) Vo ~ 5.11V
Io(max) ~ 2A DS pag. 5
Vo = 1.23 * (R3/R4 + 1) Vo ~ 4.31V
Decouple
5V & 3.3V Regulator
4.2V Regulator
Battery charger
Battery protection
Main power input
Battery connections
Power rails sense
Battery voltage sense
Coef. = 47/347 ~ 0.13545
Coef. = 100/200 = 0.5
Coef. = 47/147 ~ 0.31973
